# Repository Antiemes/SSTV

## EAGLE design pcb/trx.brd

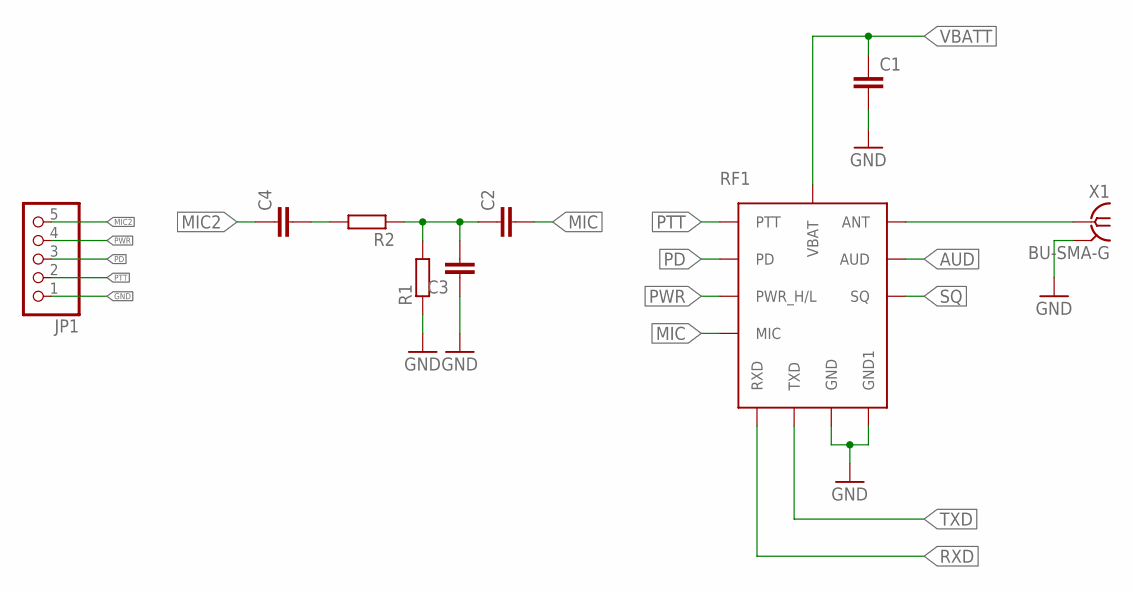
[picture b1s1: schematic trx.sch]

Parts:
C1, C2, C3, C4: C-EUC1206; C1206
JP1: PINHD-1X5; 1X05
R1, R2: R-EU_M1206; M1206
RF1: DRA818U; DRA8XXZ
X1: BU-SMA-G

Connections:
ANT: RF1.P$12 (ANT), X1.1
AUD: RF1.P$3 (AUD)
GND: C1.2, C3.1, JP1.1, R1.1, RF1.P$9 (GND), RF1.P$10 (GND1), X1.2, X1.3 (2), X1.4 (2), X1.5 (2)
MIC: C2.2, RF1.P$18 (MIC)
MIC2: C4.1, JP1.5
unnamed: C2.1, C3.2, R1.2, R2.1
unnamed: C4.2, R2.2
PD: JP1.3, RF1.P$6 (PD)
PTT: JP1.2, RF1.P$5 (PTT)
PWR: JP1.4, RF1.P$7 (PWR_H/L)
RXD: RF1.P$16 (RXD)
SQ: RF1.P$1 (SQ)
TXD: RF1.P$17 (TXD)
VBATT: C1.1, RF1.P$8 (VBAT)

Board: 2 copper layers, 9 parts (0 on the bottom side), 10 nets, no tracks yet.

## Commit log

2019-10-28 Copid from non-version-controlled repo.
2019-12-29 Moved.
2019-12-29 SSTV-CAM code added
2019-12-29 Removed old files.
2019-12-30 Removed Vim swap file.
2019-12-30 Camera firmware added.
2019-12-30 Radio module control + PTT added.
2020-01-01 Begin and end of message.
2020-01-01 VIS code added.
2020-01-01 Begin and end sequence added, untested.
2020-01-03 VIS code and DDS frequency scaling corrected.
